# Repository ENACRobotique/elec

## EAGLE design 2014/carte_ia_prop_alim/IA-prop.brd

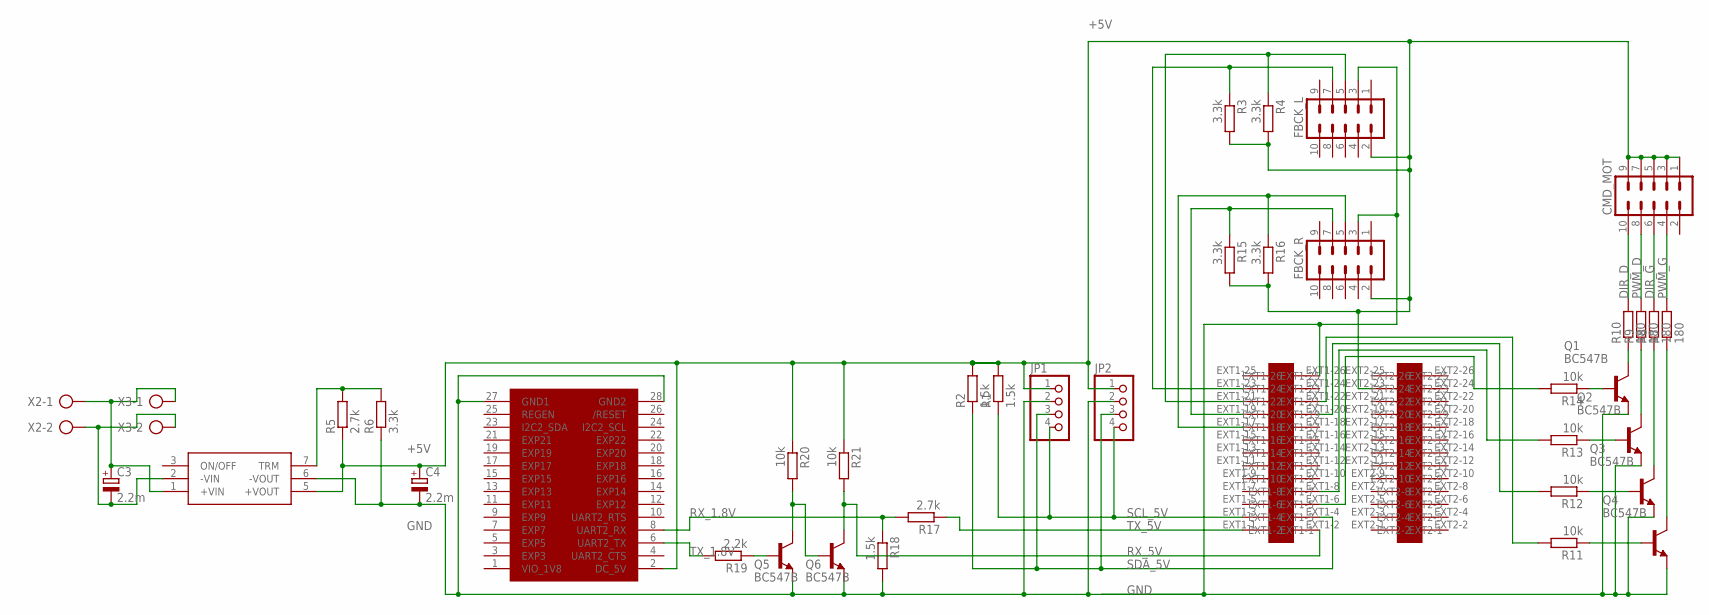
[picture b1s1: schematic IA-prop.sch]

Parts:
BB1: BEAGLEBOARD
C3, C4: 2.2m; E5-13
CMD_MOT: MA05-2
FBCK_L: MA05-2
FBCK_R: MA05-2
JP1, JP2: PINHD-1X4; 1X04
Q1, Q2, Q3, Q4, Q5, Q6: BC547B; TO92
R1: 1.5k; 0207/12
R2, R18: 1.5k; 0207/7
R3, R4, R6, R15, R16: 3.3k; 0207/7
R5: 2.7k; 0207/7
R7, R8, R9, R10: 180; 0207/7
R11, R12: 10k; 0207/10
R13, R14, R20, R21: 10k; 0207/7
R17: 2.7k; 0207/10
R19: 2.2k; 0207/7
U$1: LPC-H2148LPC-H2148; LPC-H2148
U$2: TEN25-1211TEN25-1211; TEN25
X2, X3: AK300/2

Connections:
+5V: BB1.2 (DC_5V), C4.+, CMD_MOT.1, CMD_MOT.3, CMD_MOT.5, CMD_MOT.7, CMD_MOT.9, FBCK_L.2, FBCK_R.2, JP1.1, JP2.1, R1.2, R2.2, R3.2, R4.2, R5.1, R15.2, R16.2, R20.1, R21.1, U$1.EXT2-23, U$2.5 (+VOUT)
+12V: C3.+, U$2.1 (+VIN), X2.1, X3.1
DIR_D: CMD_MOT.10, R10.2
DIR_G: CMD_MOT.6, R8.2
GND: BB1.27 (GND1), BB1.28 (GND2), C4.-, FBCK_L.3, FBCK_R.3, JP1.2, JP2.2, Q1.1 (E), Q2.1 (E), Q3.1 (E), Q4.1 (E), Q5.1 (E), Q6.1 (E), R6.1, R18.2, U$1.EXT1-26, U$2.6 (-VOUT)
GND_12: C3.-, U$2.2 (-VIN), X2.2, X3.2
unnamed: R5.2, R6.2, U$2.7 (TRM)
unnamed: R13.2, U$1.EXT1-8
unnamed: R12.2, U$1.EXT1-20
unnamed: FBCK_L.7, R3.1, U$1.EXT1-23
unnamed: R11.2, U$1.EXT1-22
unnamed: Q5.2 (B), R19.1
unnamed: Q5.3 (C), Q6.2 (B), R20.2
unnamed: FBCK_R.7, R15.1, U$1.EXT1-19
unnamed: Q1.3 (C), R10.1
unnamed: Q2.3 (C), R9.1
unnamed: Q3.3 (C), R8.1
unnamed: Q4.3 (C), R7.1
unnamed: Q1.2 (B), R14.1
unnamed: Q2.2 (B), R13.1
unnamed: Q3.2 (B), R12.1
unnamed: Q4.2 (B), R11.1
unnamed: R14.2, U$1.EXT1-6
unnamed: FBCK_R.5, R16.1, U$1.EXT1-17
unnamed: FBCK_L.5, R4.1, U$1.EXT1-21
PWM_D: CMD_MOT.8, R9.2
PWM_G: CMD_MOT.4, R7.2
RX_1.8V: BB1.8 (UART2_RX), R17.2, R18.1
RX_5V: Q6.3 (C), R21.2, U$1.EXT1-2
SCL_5V: JP1.4, JP2.4, R1.1, U$1.EXT1-3
SDA_5V: JP1.3, JP2.3, R2.1, U$1.EXT1-4
TX_1.8V: BB1.6 (UART2_TX), R19.2
TX_5V: R17.1, U$1.EXT1-1

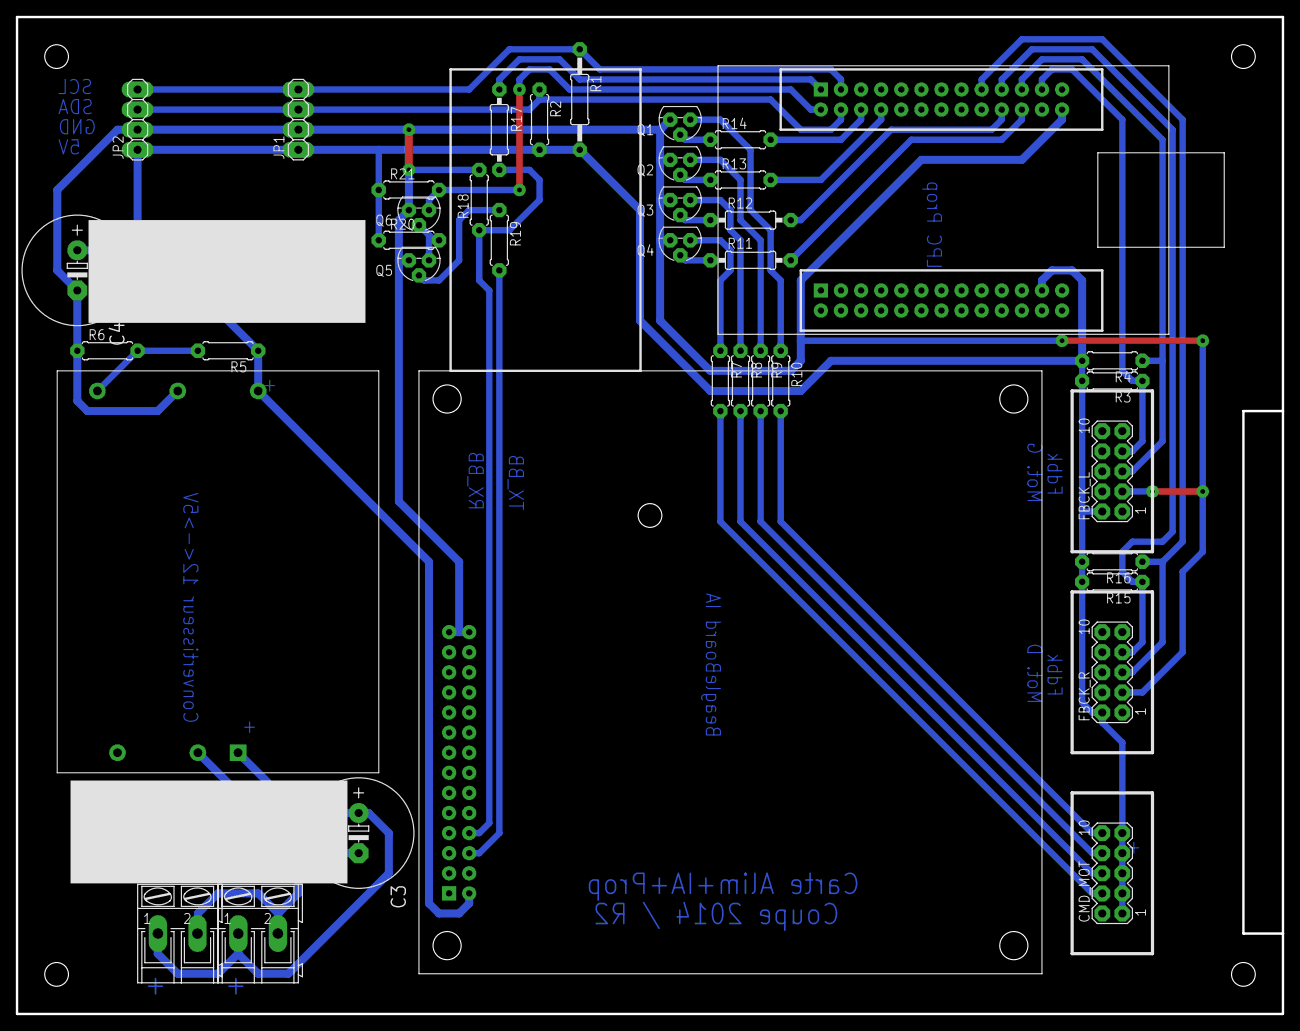
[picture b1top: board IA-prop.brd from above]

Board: 2 copper layers, 160.0 x 126.0 mm, 39 parts (0 on the bottom side), 33 nets.

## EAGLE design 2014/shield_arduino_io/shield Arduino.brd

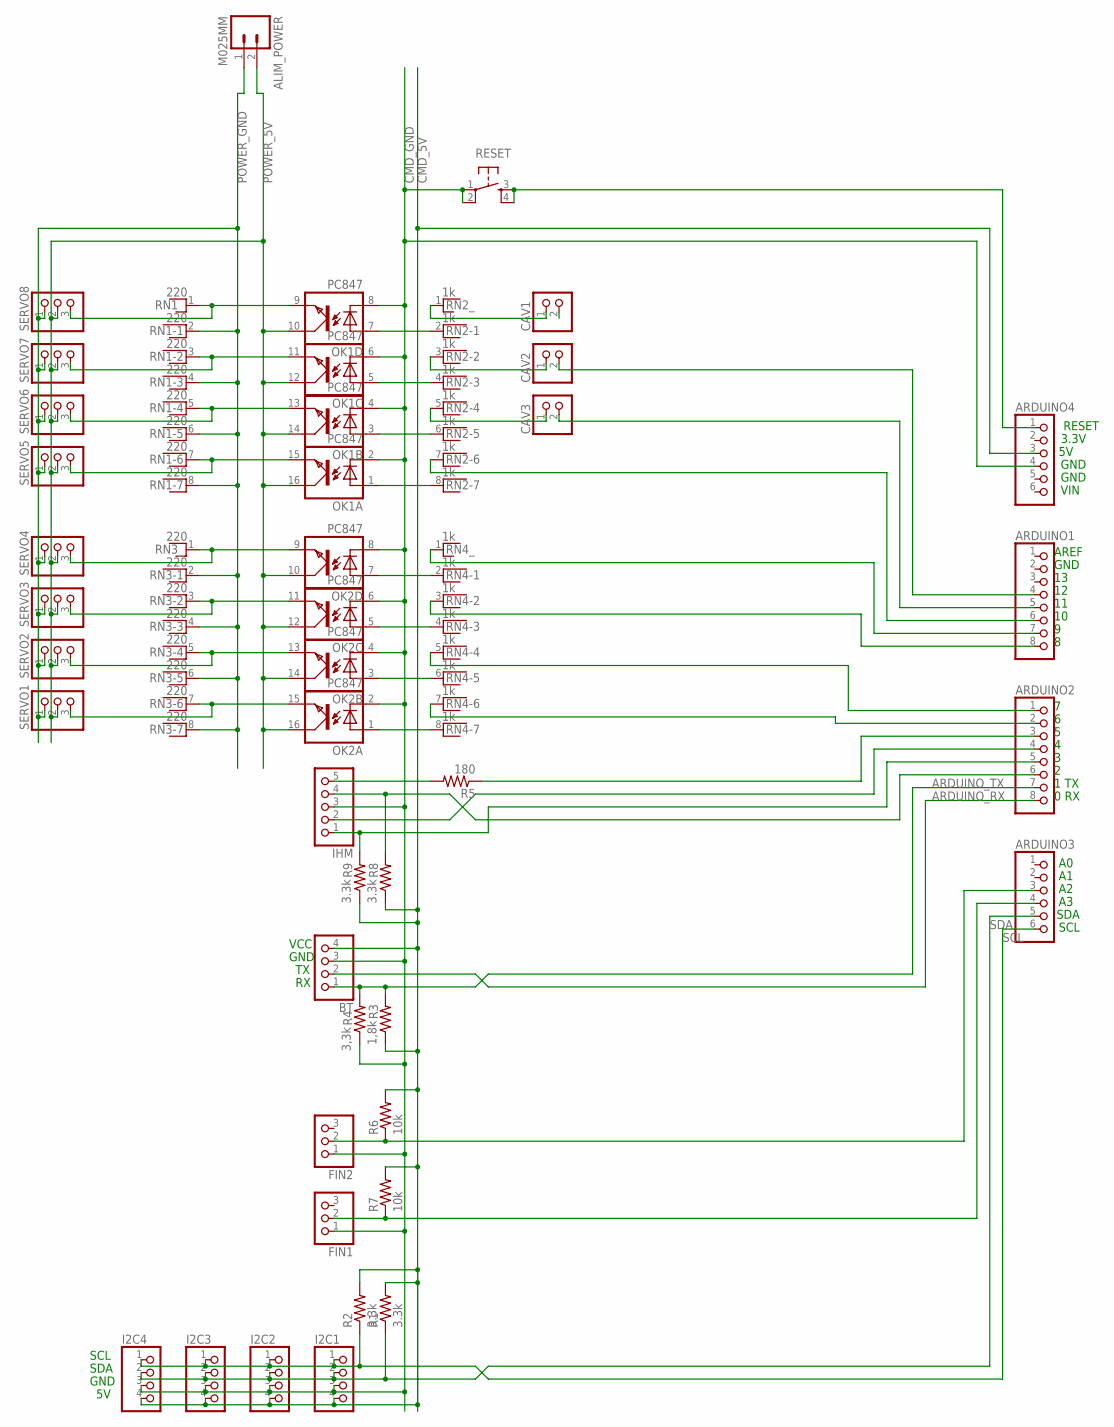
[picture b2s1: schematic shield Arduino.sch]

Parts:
ALIM_POWER: M025MM; SCREWTERMINAL-5MM-2
ARDUINO1, ARDUINO2: PINHD-1X8; 1X08
ARDUINO3, ARDUINO4: PINHD-1X6; 1X06
BT: PINHD-1X4; 1X04
CAV1, CAV2, CAV3: PINHD-1X2; 1X02
FIN1, FIN2: PINHD-1X3; 1X03
I2C1, I2C2, I2C3, I2C4: PINHD-1X4; 1X04
IHM: PINHD-1X5; 1X05
OK1, OK2: PC847; DIL16
R1, R2, R8, R9: 3.3k; 0204/7
R3: 1,8k; 0204/7
R4: 3,3k; 0204/7
R5: 180; 0204/7
R6, R7: 10k; 0204/7
RESET: TAC_SWITCHPTH; TACTILE-PTH
RN1, RN3: 220; RN-8
RN2, RN4: 1k; RN-8
SERVO1, SERVO2, SERVO3, SERVO4, SERVO5, SERVO6, SERVO7, SERVO8: PINHD-1X3; 1X03

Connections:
ARDUINO_RX: ARDUINO2.8, BT.2
ARDUINO_TX: ARDUINO2.7, BT.1, R3.2, R4.2
CMD_5V: ARDUINO4.3, BT.4, I2C1.4, I2C2.4, I2C3.4, I2C4.4, R1.2, R2.2, R3.1, R6.2, R7.2, R8.1, R9.1
CMD_GND: ARDUINO4.4, BT.3, FIN1.1, FIN2.1, I2C1.3, I2C2.3, I2C3.3, I2C4.3, IHM.3, OK1.2 (C), OK1.4 (C), OK1.6 (C), OK1.8 (C), OK2.2 (C), OK2.4 (C), OK2.6 (C), OK2.8 (C), R4.1, RESET.1, RESET.2
unnamed: OK2.7 (A), RN4.2
unnamed: ARDUINO1.4, CAV2.2
unnamed: OK2.5 (A), RN4.4
unnamed: OK2.3 (A), RN4.6
unnamed: OK1.15 (EMIT), RN1.7, SERVO5.3
unnamed: OK1.9 (EMIT), RN1.1, SERVO8.3
unnamed: ARDUINO1.5, CAV3.2
unnamed: OK2.1 (A), RN4.8
unnamed: OK1.11 (EMIT), RN1.3, SERVO7.3
unnamed: OK1.13 (EMIT), RN1.5, SERVO6.3
unnamed: OK1.1 (A), RN2.8
unnamed: OK1.3 (A), RN2.6
unnamed: OK1.5 (A), RN2.4
unnamed: OK1.7 (A), RN2.2
unnamed: CAV1.1, RN2.1
unnamed: CAV2.1, RN2.3
unnamed: CAV3.1, RN2.5
unnamed: ARDUINO1.6, RN2.7
unnamed: OK2.15 (EMIT), RN3.7, SERVO1.3
unnamed: OK2.9 (EMIT), RN3.1, SERVO4.3
unnamed: OK2.11 (EMIT), RN3.3, SERVO3.3
unnamed: OK2.13 (EMIT), RN3.5, SERVO2.3
unnamed: ARDUINO4.1, RESET.3, RESET.4
unnamed: ARDUINO1.7, RN4.1
unnamed: ARDUINO1.8, RN4.3
unnamed: ARDUINO2.1, RN4.5
unnamed: ARDUINO2.2, RN4.7
unnamed: IHM.5, R5.2
unnamed: ARDUINO3.4, FIN1.2, R7.1
unnamed: ARDUINO3.3, FIN2.2, R6.1
unnamed: ARDUINO2.3, R5.1
unnamed: ARDUINO2.5, IHM.1, R9.2
unnamed: ARDUINO2.4, IHM.2
unnamed: ARDUINO2.6, IHM.4, R8.2
POWER_5V: ALIM_POWER.2, OK1.10 (COL), OK1.12 (COL), OK1.14 (COL), OK1.16 (COL), OK2.10 (COL), OK2.12 (COL), OK2.14 (COL), OK2.16 (COL), SERVO1.2, SERVO2.2, SERVO3.2, SERVO4.2, SERVO5.2, SERVO6.2, SERVO7.2, SERVO8.2
POWER_GND: ALIM_POWER.1, RN1.2, RN1.4, RN1.6, RN1.8, RN3.2, RN3.4, RN3.6, RN3.8, SERVO1.1, SERVO2.1, SERVO3.1, SERVO4.1, SERVO5.1, SERVO6.1, SERVO7.1, SERVO8.1
SCL: ARDUINO3.6, I2C1.1, I2C2.1, I2C3.1, I2C4.1, R2.1
SDA: ARDUINO3.5, I2C1.2, I2C2.2, I2C3.2, I2C4.2, R1.1

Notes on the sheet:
SDA
SCL
0 RX
1 TX
GND
AREF
VIN
3.3V
RESET
VCC

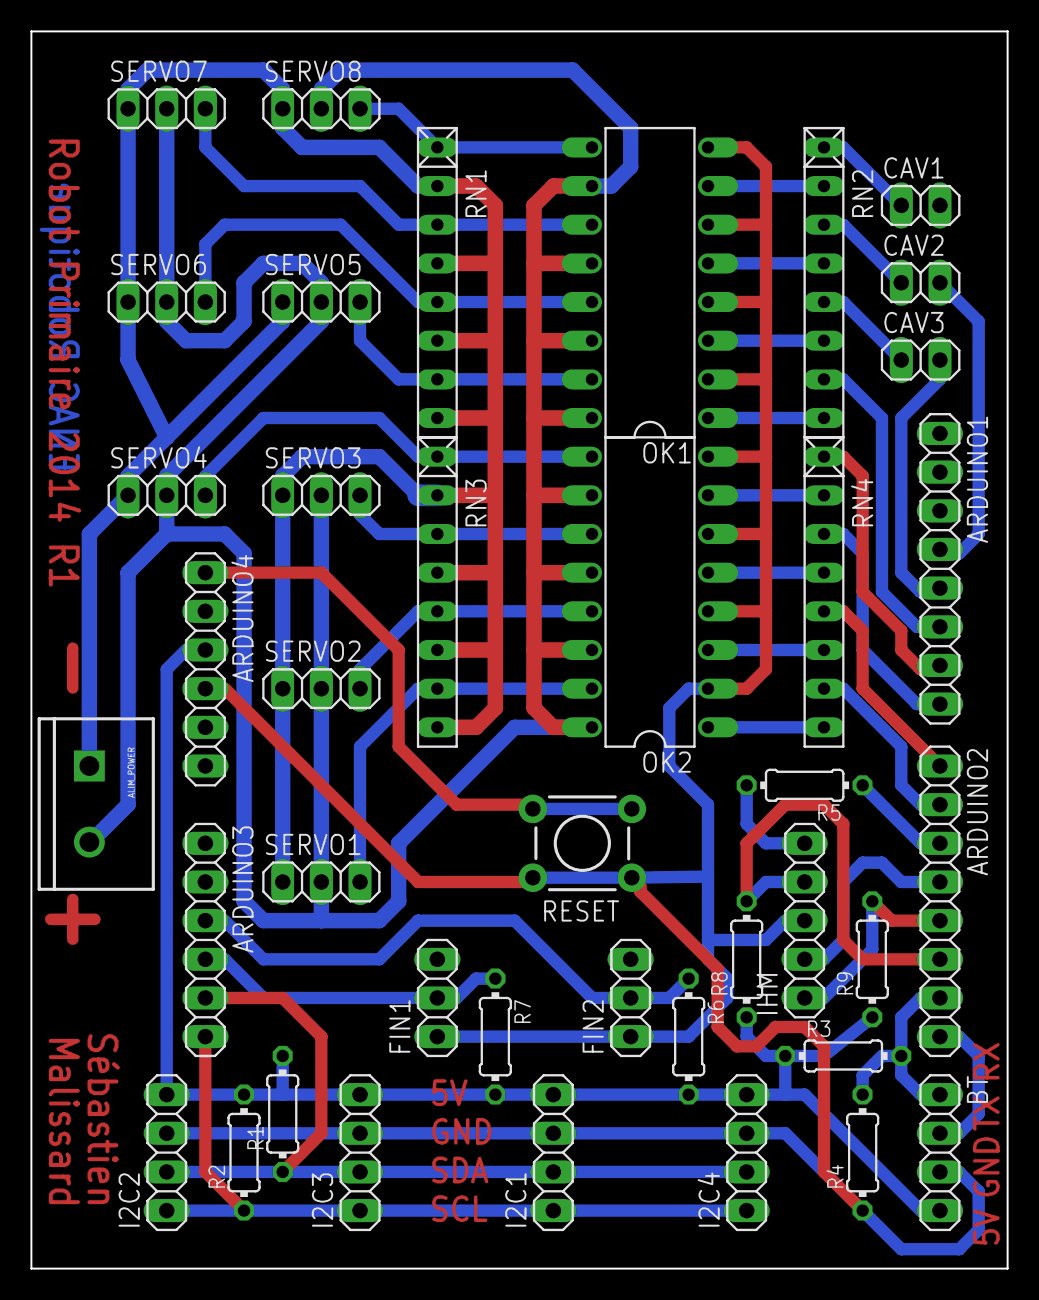
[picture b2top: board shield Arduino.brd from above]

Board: 2 copper layers, 64.1 x 81.3 mm, 40 parts (0 on the bottom side), 42 nets.

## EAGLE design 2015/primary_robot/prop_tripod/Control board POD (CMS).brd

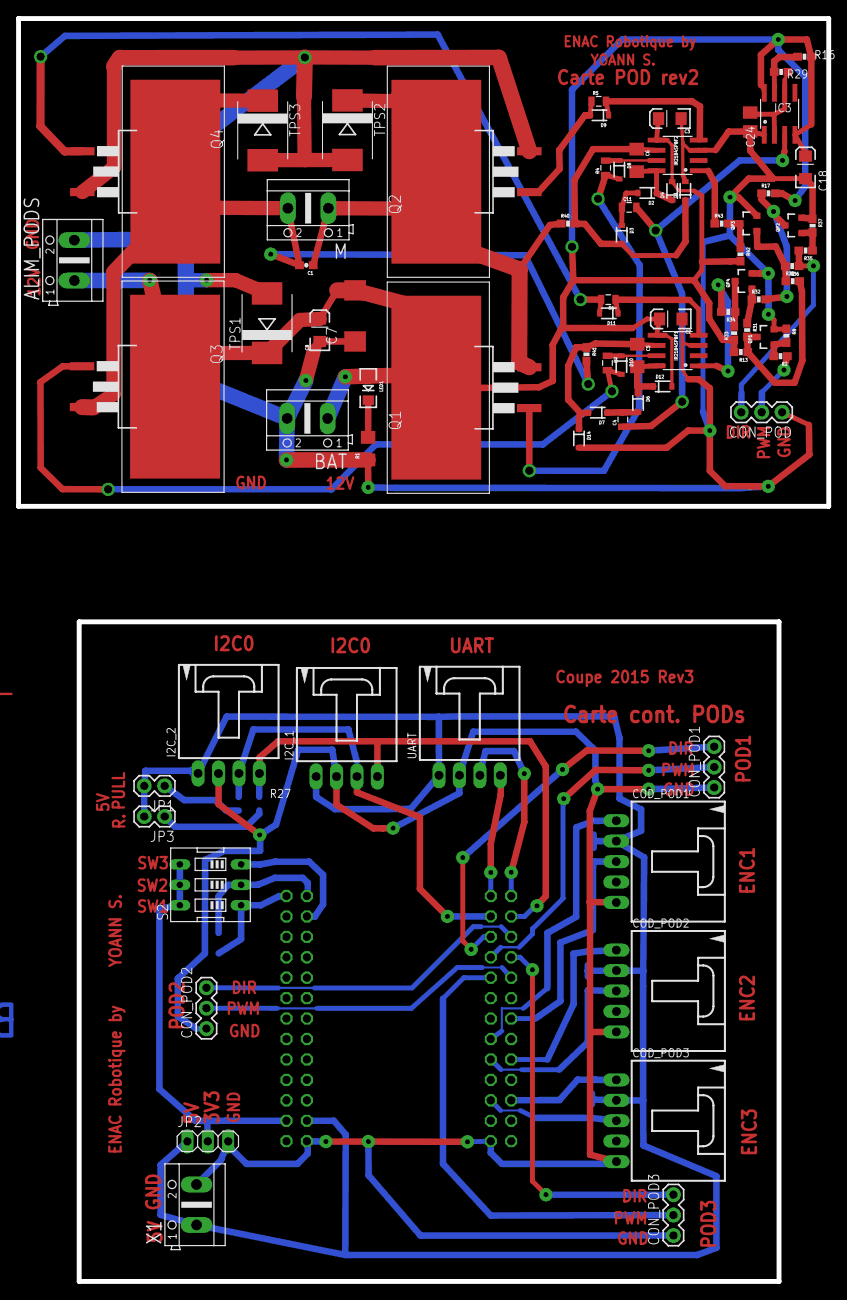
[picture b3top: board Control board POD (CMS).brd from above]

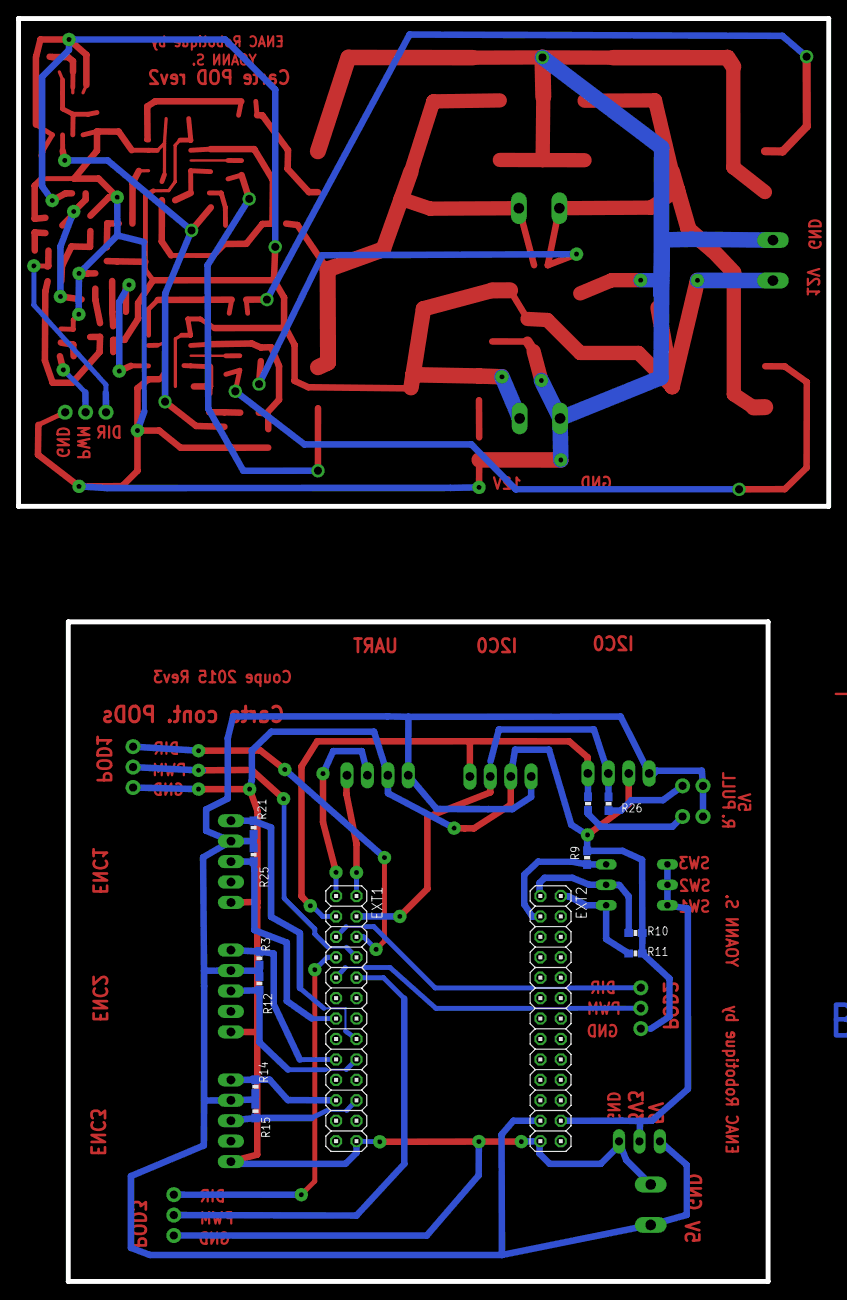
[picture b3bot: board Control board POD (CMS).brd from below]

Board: 2 copper layers, 100.7 x 157.0 mm, 92 parts (13 on the bottom side), 58 nets.

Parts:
ALIM_PODS: 12; AK500/2
BAT: 12; AK500/2
C1: 1uF; 0603-CAP
C2, C3, C18: 10uF; EIA3216
C4, C11: 680nF; 0805
C5, C6: 680nF; 1206
C7: 220uF; D/7343-31R
C8: 220nF; EIA3216
C24: 100nF; R/2012-12R
COD_POD1, COD_POD2, COD_POD3: C-GRID-05-70553; 70553-05
CON_POD, CON_POD1, CON_POD2, CON_POD3: 1X03
D1, D2, D3, D4, D6, D7, D8, D9, D10, D11, D12, D14: SOD-323
EXT1, EXT2: 2X13
I2C_1, I2C_2: C-GRID-04-70553; 70553-04
IC3: NE555D; SO08
IR2184SPBF1, IR2184SPBF2: IR2184SPBF; SO08
JP1, JP3: 1X02
JP2: 1X03
LED1: LED-1206
M: AK500/2
Q1, Q2, Q3, Q4: MOSFET-NCHANNELD2PAK; D2PAK-3
QP1, QP2, QP3, QP4: SOT23-3
R1: 560; 1206
R2, R8, R9, R10, R11, R29, R31, R32, R34, R35, R36, R37, R38, R43: 10k; 0603-RES
R3, R12, R14, R15, R21, R25: 3k3; 0603-RES
R4, R5, R6, R7: 15; 0805
R13, R16, R17, R33, R42: 1k; 0603-RES
R26, R27: 3.3k; 0603-RES
R40, R41: 15; 0603-RES
S2: EDG-03
TPS1, TPS2, TPS3: SMC
UART: C-GRID-04-70553; 70553-04
X1: AK500/2

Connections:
3V3: EXT2.24, JP2.2, S2.4, S2.5, S2.6
5V_CMD: COD_POD1.2, COD_POD2.2, COD_POD3.2, EXT2.23, I2C_1.1, I2C_2.1, JP1.2, JP2.1, JP3.2, R3.2, R12.1, R14.2, R15.1, R21.2, R25.1, UART.1, X1.1
12V_BAT: ALIM_PODS.1, BAT.1, C2.A, C3.A, C7.+, C8.A, C18.A, D4.A, D12.A, IC3.4, IC3.8, IR2184SPBF1.5, IR2184SPBF2.5, LED1.A, Q1.4, Q3.4, R13.2, R16.2, R17.2, R33.1, R42.2, TPS1.C
BSTRP: C4.1, C11.2, IC3.3
CHA_POD1_LPC: COD_POD1.3, EXT1.13, R25.2
CHA_POD2_LPC: COD_POD2.3, EXT1.18, R12.2
CHA_POD3_LPC: COD_POD3.3, EXT1.22, R15.2
CHB_POD1_LPC: COD_POD1.1, EXT1.16, R21.1
CHB_POD2_LPC: COD_POD2.1, EXT1.17, R3.1
CHB_POD3_LPC: COD_POD3.1, EXT1.21, R14.1
DIR: CON_POD.3, R35.2, R36.1
DIR_POD1_LPC: CON_POD1.3, EXT1.6
DIR_POD2_LPC: CON_POD2.3, EXT1.5
DIR_POD3_LPC: CON_POD3.3, EXT1.7
GATE_Q3: D9.A, Q2.1, R5.1
GATE_Q4: D10.A, Q3.1, R7.2
GND_CMD: COD_POD1.5, COD_POD2.5, COD_POD3.5, CON_POD1.1, CON_POD2.1, CON_POD3.1, EXT1.26, EXT2.25, I2C_1.2, I2C_2.2, JP2.3, R9.2, R10.2, R11.2, UART.2, X1.2
GND_PWR: ALIM_PODS.2, BAT.2, C2.C, C3.C, C7.-, C8.C, C18.C, C24.-, CON_POD.1, D1.A, D14.A, IC3.1, IR2184SPBF1.3, IR2184SPBF2.3, Q2.3, Q4.3, QP1.2, QP2.2, QP3.2, QP4.2, R1.1, R8.1, R37.1, TPS1.A, TPS2.A, TPS3.A
HO_A: D8.C, IR2184SPBF2.7, R4.2
HO_B: D10.C, IR2184SPBF1.7, R7.1
IN1: IR2184SPBF1.1, R34.2
IN2: IR2184SPBF2.1, R43.1
LO_A: D9.C, IR2184SPBF2.4, R5.2
LO_B: D11.C, IR2184SPBF1.4, R6.1
unnamed: C11.1, D2.A, D3.C
unnamed: D8.A, Q1.1, R4.1
unnamed: C1.2, M.2, Q3.3, Q4.4, R41.2, TPS3.C
unnamed: C6.2, D2.C, D4.C, IR2184SPBF2.8
unnamed: C4.2, D6.A, D7.C
unnamed: C5.2, D6.C, D12.C, IR2184SPBF1.8
unnamed: LED1.C, R1.2
unnamed: C1.1, M.1, Q1.3, Q2.4, R40.1, TPS2.C
unnamed: D11.A, Q4.1, R6.2
unnamed: IC3.7, R16.1, R29.2
unnamed: C24.+, IC3.2, IC3.6, R29.1
unnamed: JP1.1, R26.1
unnamed: QP1.1, R2.2, R8.2
unnamed: JP3.1, R27.1
unnamed: QP2.1, R35.1, R37.2
unnamed: QP3.1, R36.2, R38.1
unnamed: QP1.3, R13.1, R31.2, R38.2
unnamed: QP4.1, R31.1, R32.1
unnamed: QP2.3, R17.1, R32.2
unnamed: QP4.3, R33.2, R34.1
unnamed: QP3.3, R42.1, R43.2
PWM: CON_POD.2, R2.1
PWM_POD1_LPC: CON_POD1.2, EXT1.8
PWM_POD2_LPC: CON_POD2.2, EXT1.9
PWM_POD3_LPC: CON_POD3.2, EXT1.10
RX0_LPC: EXT1.2, UART.4
SCL0_LPC: EXT1.3, I2C_1.4, I2C_2.4, R27.2
SDA0_LPC: EXT1.4, I2C_1.3, I2C_2.3, R26.2
SW1_LPC: EXT2.1, R10.1, S2.2
SW2_LPC: EXT2.2, R11.1, S2.1
SW3_LPC: EXT2.3, R9.1, S2.3
TX0_LPC: EXT1.1, UART.3
VS_A: C6.1, D1.C, D3.A, IR2184SPBF2.6, R40.2
VS_B: C5.1, D7.A, D14.C, IR2184SPBF1.6, R41.1

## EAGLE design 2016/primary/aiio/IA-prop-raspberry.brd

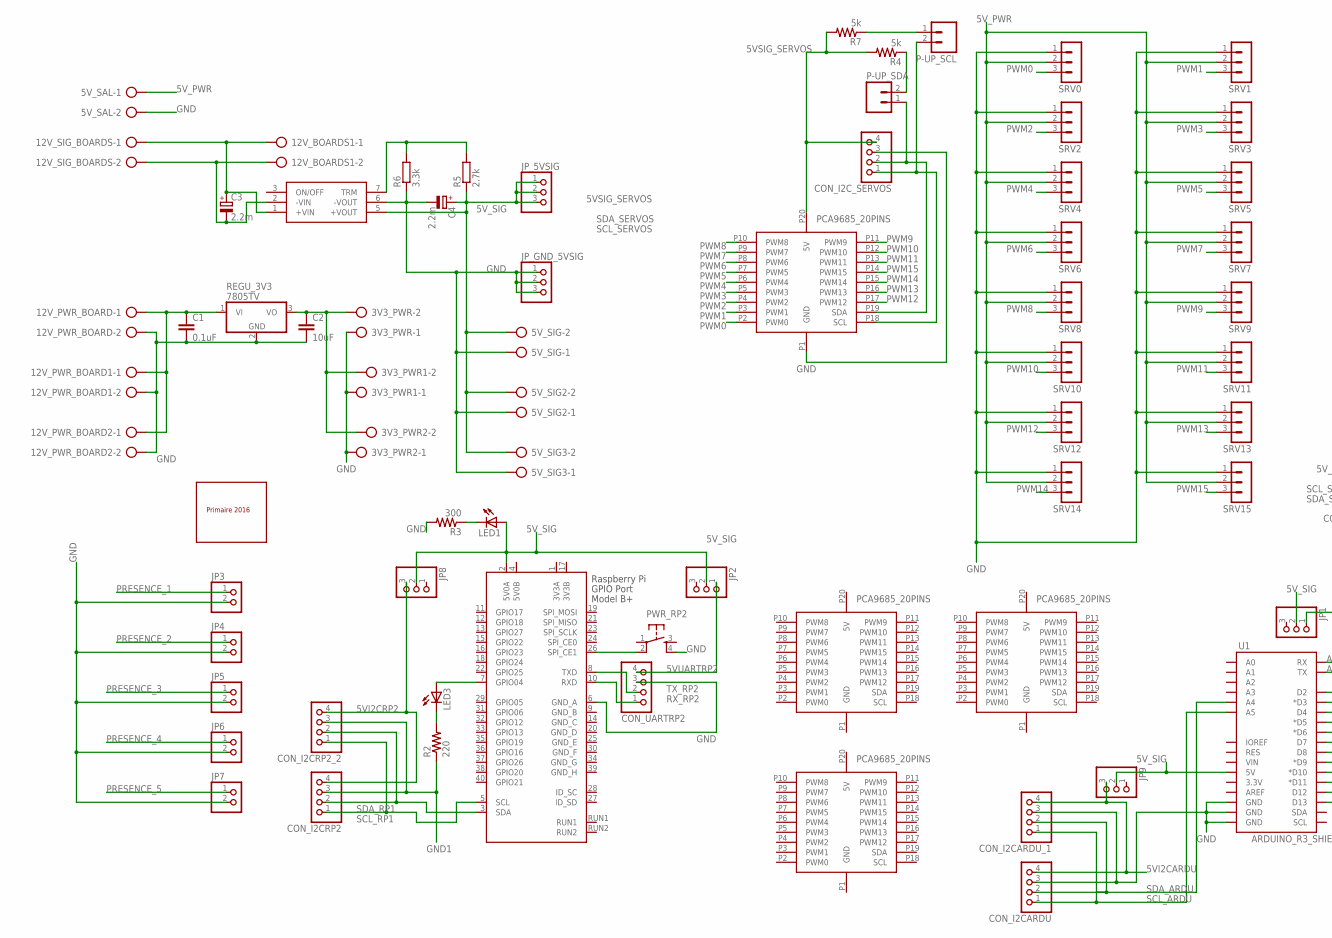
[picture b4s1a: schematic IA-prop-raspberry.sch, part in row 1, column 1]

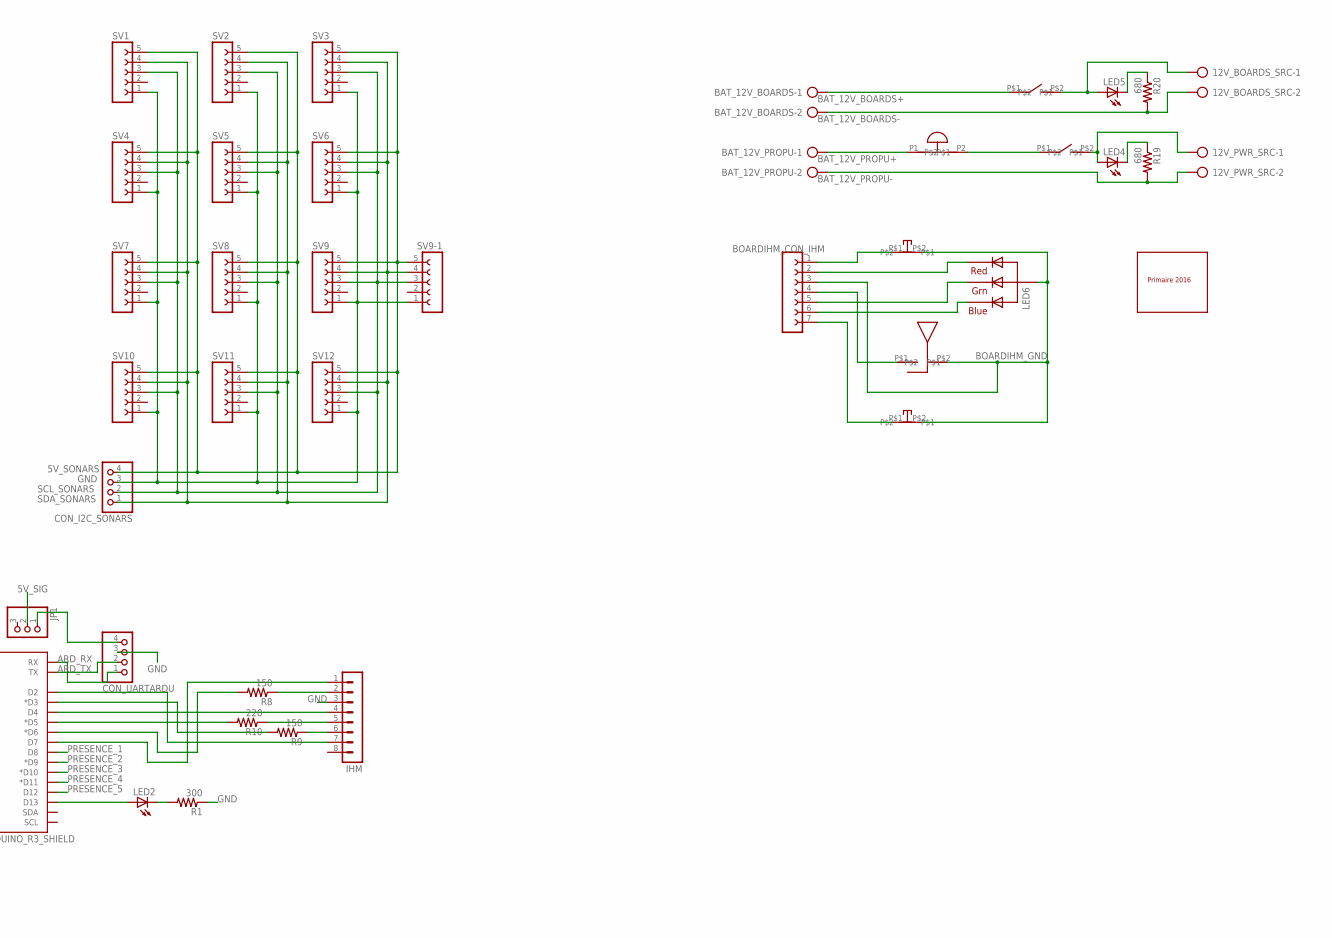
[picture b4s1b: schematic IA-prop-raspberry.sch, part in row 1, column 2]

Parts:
3V3_PWR, 3V3_PWR1, 3V3_PWR2, 5V_SAL, 5V_SIG, 5V_SIG2, 5V_SIG3, 12V_BOARDS1, 12V_BOARDS_SRC, 12V_PWR_BOARD, 12V_PWR_BOARD1, 12V_PWR_BOARD2, 12V_PWR_SRC, 12V_SIG_BOARDS: AK300/2
BAT_12V_BOARDS, BAT_12V_PROPU: AK300/2
BOARDIHM_CON_IHM: FE07-1; FE07
C1: 0.1uF; C050-025X075
C2: 10uF; C050-025X075
C3, C4: 2.2m; E5-13
CON_I2CARDU, CON_I2CARDU_1, CON_I2CRP2, CON_I2CRP2_2, CON_I2C_SERVOS, CON_I2C_SONARS: PINHD-1X4; 1X04
CON_UARTARDU: PINHD-1X4; 1X04
CON_UARTRP2: PINHD-1X4; 1X04
IHM: MA08-1
JP1, JP2, JP8, JP9: PINHD-1X3; 1X03
JP3, JP4, JP5, JP6, JP7: PINHD-1X2; 1X02
JP_5VSIG: PINHD-1X3; 1X03
JP_GND_5VSIG: PINHD-1X3; 1X03
LED1, LED2, LED3: LED3MM
LED4, LED5: LED5MM
LED6: RGBLED_CA-5MM; LED5MMRGB
P-UP_SCL: M02PTH; 1X02
P-UP_SDA: M02PTH; 1X02
PWR_RP2: TAC_SWITCHPTH; TACTILE-PTH
R1, R3: 300; AXIAL-0.3
R2, R10: 220; AXIAL-0.3
R4, R7: 5k; AXIAL-0.3
R5: 2.7k; 0207/7
R6: 3.3k; 0207/7
R8, R9: 150; AXIAL-0.3
R19, R20: 680; AXIAL-0.3
REGU_3V3: 7805TV; TO220V
RP2: RASPI_BOARD_B+#_FP; RASPI_BOARD_B+_FULL_PAD
SRV0, SRV1, SRV2, SRV3, SRV4, SRV5, SRV6, SRV7, SRV8, SRV9, SRV10, SRV11, SRV12, SRV13, SRV14, SRV15: MA03-1
SV1, SV2, SV3, SV4, SV5, SV6, SV7, SV8, SV9, SV9-1, SV10, SV11, SV12: FE05-1
U1: ARDUINO_R3_SHIELD; UNO_R3_SHIELD
U$1: PCA9685_FEMALE; 2X10PINS_SPACE10MM
U$2: TEN25-1211TEN25-1211; TEN25
U$3, U$11: FOOTPRINT_PRIMAIRE2016; PRIMAIRE2016
U$4: BAU; BAU_30
U$5, U$7, U$13: PCA9685_MALE; TSSOP28_&_2X10PINS_SPACE10MM
U$6, U$8: SWITCH_01
U$9, U$12: PUSH_BUT_COL_SELEC
U$10: CORD

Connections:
3V3A: RP2.1 (3V3A)
3V3B: RP2.17 (3V3B)
5V0B: RP2.4 (5V0B)
5VI2CARDU: CON_I2CARDU.4, CON_I2CARDU_1.4, JP9.3
5VI2CRP2: CON_I2CRP2.4, CON_I2CRP2_2.4, JP8.3
5VSIG_SERVOS: CON_I2C_SERVOS.4, R4.P$2 (2), R7.P$2 (2), U$1.P20 (5V)
5VUARTRP2: CON_UARTRP2.4, JP2.1
5V_PRP1: LED2.A, U1.D13
5V_PWR: 5V_SAL.1, SRV0.2, SRV1.2, SRV2.2, SRV3.2, SRV4.2, SRV5.2, SRV6.2, SRV7.2, SRV8.2, SRV9.2, SRV10.2, SRV11.2, SRV12.2, SRV13.2, SRV14.2, SRV15.2
5V_SIG: 5V_SIG.2, 5V_SIG2.2, 5V_SIG3.2, C4.+, JP1.2, JP2.2, JP8.2, JP9.2, JP_5VSIG.1, JP_5VSIG.2, JP_5VSIG.3, LED1.A, R5.1, RP2.2 (5V0A), U1.5V, U$2.5 (+VOUT)
5V_SONARS: CON_I2C_SONARS.4, SV1.5, SV2.5, SV3.5, SV4.5, SV5.5, SV6.5, SV7.5, SV8.5, SV9.5, SV9-1.5, SV10.5, SV11.5, SV12.5
+12V: 12V_BOARDS1.1, 12V_SIG_BOARDS.1, C3.+, U$2.1 (+VIN)
ARD_RX: CON_UARTARDU.1, U1.RX
ARD_TX: CON_UARTARDU.2, U1.TX
BAT_12V_BOARDS+: BAT_12V_BOARDS.1, U$8.P$1
BAT_12V_BOARDS-: 12V_BOARDS_SRC.2, BAT_12V_BOARDS.2, R20.P$2 (2)
BAT_12V_PROPU+: BAT_12V_PROPU.1, U$4.P1
BAT_12V_PROPU-: 12V_PWR_SRC.2, BAT_12V_PROPU.2, R19.P$2 (2)
BOARDIHM_GND: BOARDIHM_CON_IHM.3, LED6.2 (VCC), U$9.P$2, U$10.P$2, U$12.P$2
GND: 3V3_PWR.1, 3V3_PWR1.1, 3V3_PWR2.1, 5V_SAL.2, 5V_SIG.1, 5V_SIG2.1, 5V_SIG3.1, 12V_PWR_BOARD.2, 12V_PWR_BOARD1.2, 12V_PWR_BOARD2.2, C1.2, C2.2, C4.-, CON_I2CARDU.3, CON_I2CARDU_1.3, CON_I2C_SERVOS.3, CON_I2C_SONARS.3, CON_UARTARDU.3, CON_UARTRP2.3, IHM.3, JP3.2, JP4.2, JP5.2, JP6.2, JP7.2, JP_GND_5VSIG.1, JP_GND_5VSIG.2, JP_GND_5VSIG.3, PWR_RP2.4, R1.P$1 (1), R3.P$2 (2), R6.1, REGU_3V3.2 (GND), RP2.6 (GND_A), SRV0.1, SRV1.1, SRV2.1, SRV3.1, SRV4.1, SRV5.1, SRV6.1, SRV7.1, SRV8.1, SRV9.1, SRV10.1, SRV11.1, SRV12.1, SRV13.1, SRV14.1, SRV15.1, SV1.1, SV2.1, SV3.1, SV4.1, SV5.1, SV6.1, SV7.1, SV8.1, SV9.1, SV9-1.1, SV10.1, SV11.1, SV12.1, U1.GND@0 (GND), U1.GND@1 (GND), U1.GND@2 (GND), U$1.P1 (GND), U$2.6 (-VOUT)
GND1: CON_I2CRP2.3, CON_I2CRP2_2.3, R2.P$1 (1)
GND_12: 12V_BOARDS1.2, 12V_SIG_BOARDS.2, C3.-, U$2.2 (-VIN)
GND_B: RP2.9 (GND_B)
GND_C: RP2.14 (GND_C)
GND_D: RP2.20 (GND_D)
GND_E: RP2.25 (GND_E)
GND_F: RP2.30 (GND_F)
GND_G: RP2.34 (GND_G)
GND_H: RP2.39 (GND_H)
unnamed: CON_UARTARDU.4, JP1.1
unnamed: LED2.K (C), R1.P$2 (2)
unnamed: LED3.K (C), R2.P$2 (2)
unnamed: R5.2, R6.2, U$2.7 (TRM)
unnamed: P-UP_SDA.2, R4.P$1 (1)
unnamed: BOARDIHM_CON_IHM.1, U$9.P$1
unnamed: LED1.K (C), R3.P$1 (1)
unnamed: U$4.P2, U$6.P$1
unnamed: P-UP_SCL.1, R7.P$1 (1)
unnamed: LED4.K (C), R19.P$1 (1)
unnamed: 12V_BOARDS_SRC.1, LED5.A, U$8.P$2
unnamed: BOARDIHM_CON_IHM.2, LED6.1 (RED)
unnamed: LED5.K (C), R20.P$1 (1)
unnamed: R9.P$2 (2), U1.D3 (*D3)
unnamed: BOARDIHM_CON_IHM.4, U$10.P$1
unnamed: R10.P$2 (2), U1.D5 (*D5)
unnamed: 12V_PWR_SRC.1, LED4.A, U$6.P$2
unnamed: IHM.6, R9.P$1 (1)
unnamed: LED3.A, RP2.7 (GPIO04)
unnamed: IHM.5, R10.P$1 (1)
unnamed: IHM.2, R8.P$1 (1)
unnamed: R8.P$2 (2), U1.D6 (*D6)
unnamed: IHM.1, U1.D7
unnamed: IHM.4, U1.D4
unnamed: IHM.7, U1.D2
unnamed: BOARDIHM_CON_IHM.5, LED6.3 (GREEN)
unnamed: BOARDIHM_CON_IHM.6, LED6.4 (BLUE)
unnamed: 3V3_PWR.2, 3V3_PWR1.2, 3V3_PWR2.2, C2.1, REGU_3V3.3 (VO)
unnamed: BOARDIHM_CON_IHM.7, U$12.P$1
unnamed: 12V_PWR_BOARD.1, 12V_PWR_BOARD1.1, 12V_PWR_BOARD2.1, C1.1, REGU_3V3.1 (VI)
PRESENCE_1: JP3.1, U1.D8
PRESENCE_2: JP4.1, U1.D9 (*D9)
PRESENCE_3: JP5.1, U1.D10 (*D10)
PRESENCE_4: JP6.1, U1.D11 (*D11)
PRESENCE_5: JP7.1, U1.D12
PWM0: SRV0.3, U$1.P2 (PWM0)
PWM1: SRV1.3, U$1.P3 (PWM1)
PWM2: SRV2.3, U$1.P4 (PWM2)
PWM3: SRV3.3, U$1.P5 (PWM3)
PWM4: SRV4.3, U$1.P6 (PWM4)
PWM5: SRV5.3, U$1.P7 (PWM5)
PWM6: SRV6.3, U$1.P8 (PWM6)
PWM7: SRV7.3, U$1.P9 (PWM7)
PWM8: SRV8.3, U$1.P10 (PWM8)
PWM9: SRV9.3, U$1.P11 (PWM9)
PWM10: SRV10.3, U$1.P12 (PWM10)
PWM11: SRV11.3, U$1.P13 (PWM11)
PWM12: SRV12.3, U$1.P17 (PWM12)
PWM13: SRV13.3, U$1.P16 (PWM13)
PWM14: SRV14.3, U$1.P15 (PWM14)
PWM15: SRV15.3, U$1.P14 (PWM15)
RP2_PWR: PWR_RP2.2, RP2.26 (SPI_CE1)
RX_RP2: CON_UARTRP2.1, RP2.10 (RXD)
SCL_ARDU: CON_I2CARDU.1, CON_I2CARDU_1.1, U1.A5
SCL_RP1: CON_I2CRP2.1, CON_I2CRP2_2.1, RP2.5 (SCL)
SCL_SERVOS: CON_I2C_SERVOS.1, P-UP_SCL.2, U$1.P18 (SCL)
SCL_SONARS: CON_I2C_SONARS.2, SV1.3, SV2.3, SV3.3, SV4.3, SV5.3, SV6.3, SV7.3, SV8.3, SV9.3, SV9-1.3, SV10.3, SV11.3, SV12.3
SDA_ARDU: CON_I2CARDU.2, CON_I2CARDU_1.2, U1.A4
SDA_RP1: CON_I2CRP2.2, CON_I2CRP2_2.2, RP2.3 (SDA)
SDA_SERVOS: CON_I2C_SERVOS.2, P-UP_SDA.1, U$1.P19 (SDA)
SDA_SONARS: CON_I2C_SONARS.1, SV1.4, SV2.4, SV3.4, SV4.4, SV5.4, SV6.4, SV7.4, SV8.4, SV9.4, SV9-1.4, SV10.4, SV11.4, SV12.4
TX_RP2: CON_UARTRP2.2, RP2.8 (TXD)

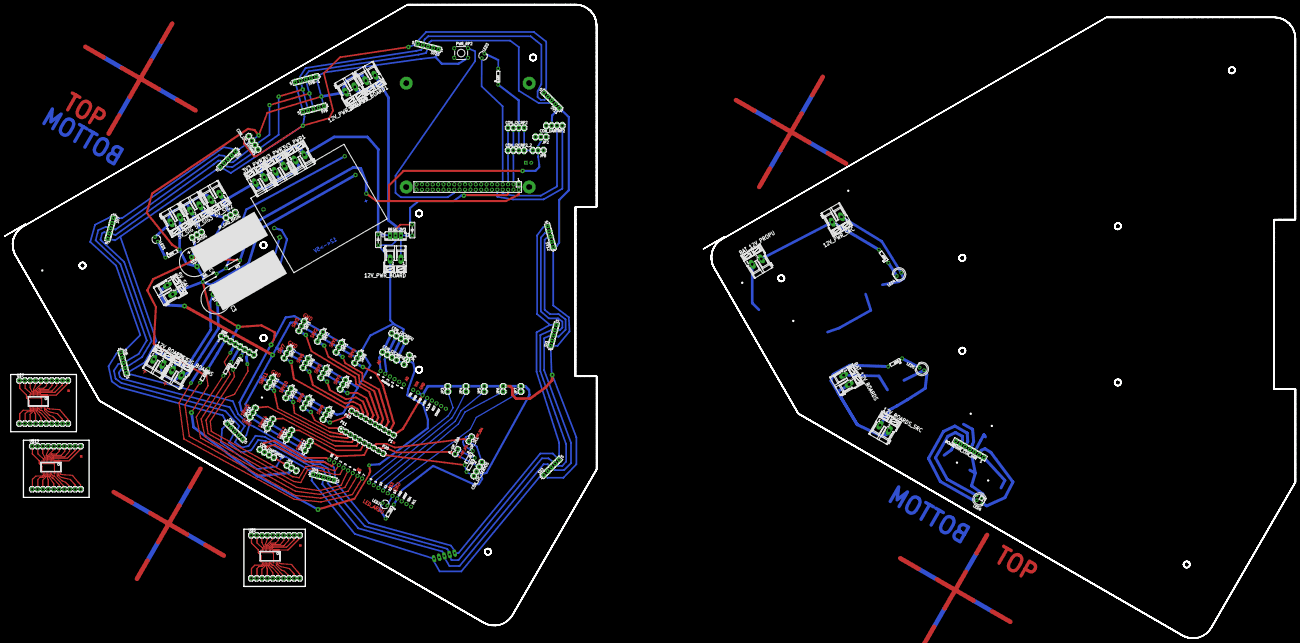
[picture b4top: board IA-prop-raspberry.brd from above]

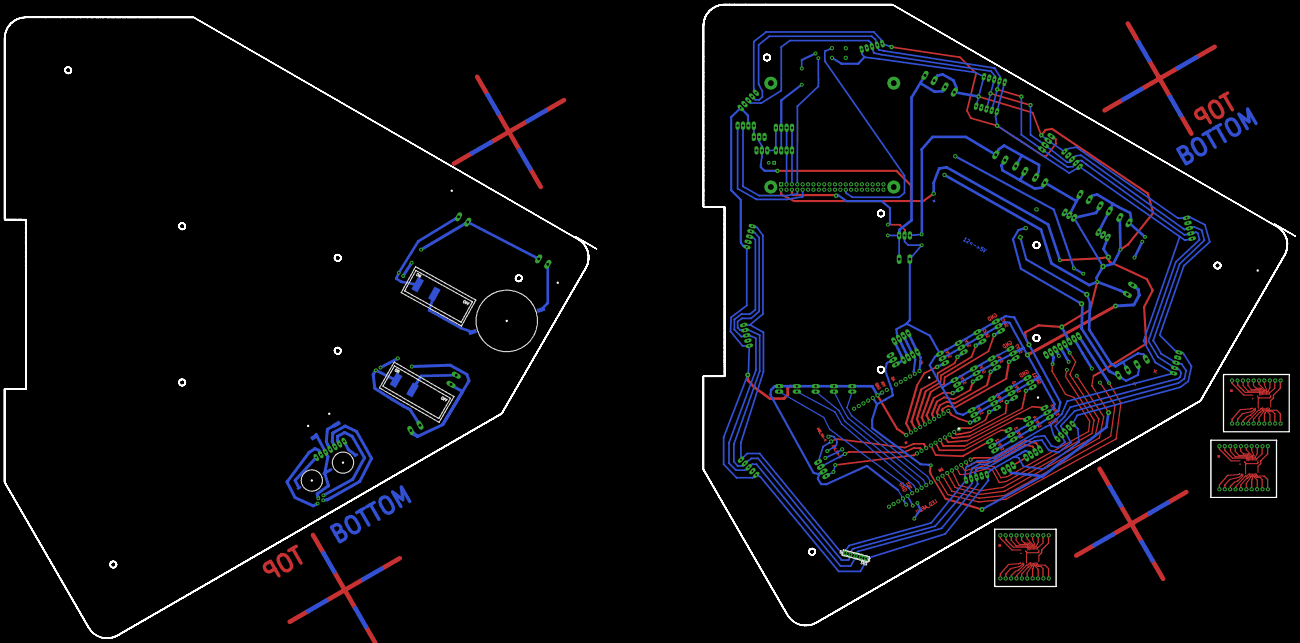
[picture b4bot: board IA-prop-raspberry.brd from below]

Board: 2 copper layers, 606.3 x 299.3 mm, 107 parts (9 on the bottom side), 81 nets.

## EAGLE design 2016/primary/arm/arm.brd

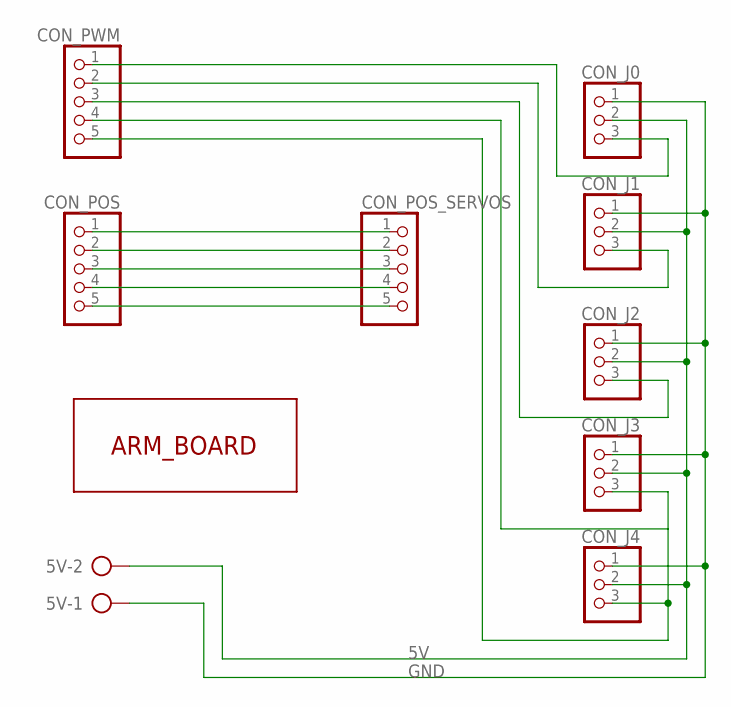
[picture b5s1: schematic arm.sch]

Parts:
5V: AK500/2
CON_J0, CON_J1, CON_J2, CON_J3, CON_J4: PINHD-1X3; 1X03
CON_POS: PINHD-1X5; 1X05
CON_POS_SERVOS: PINHD-1X5; 1X05
CON_PWM: PINHD-1X5; 1X05
U$1: ARM_BOARD

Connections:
5V: 5V.2, CON_J0.2, CON_J1.2, CON_J2.2, CON_J3.2, CON_J4.2
GND: 5V.1, CON_J0.1, CON_J1.1, CON_J2.1, CON_J3.1, CON_J4.1
POS0: CON_POS.1, CON_POS_SERVOS.1
POS1: CON_POS.2, CON_POS_SERVOS.2
POS2: CON_POS.3, CON_POS_SERVOS.3
POS3: CON_POS.4, CON_POS_SERVOS.4
POS4: CON_POS.5, CON_POS_SERVOS.5
PWM0: CON_J0.3, CON_PWM.1
PWM1: CON_J1.3, CON_PWM.2
PWM2: CON_J2.3, CON_PWM.3
PWM3: CON_J3.3, CON_PWM.4
PWM4: CON_J4.3, CON_PWM.5

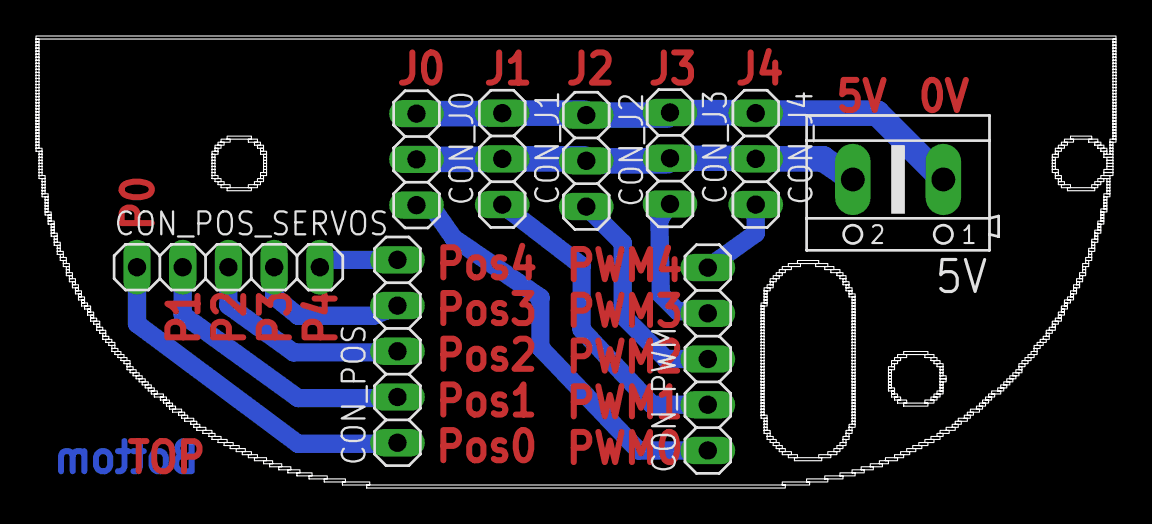
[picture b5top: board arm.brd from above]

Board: 2 copper layers, 60.0 x 25.1 mm, 10 parts (0 on the bottom side), 12 nets.

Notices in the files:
parts and their libraries:
SparkFun-Connectors: Licensing: Creative Commons ShareAlike 4.0 International - https://creativecommons.org/licenses/by-sa/4.0
SparkFun: Licensing: CC v3.0 Share-Alike You are welcome to use this library for commercial purposes.
